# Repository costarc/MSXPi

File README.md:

# MSXPi

MSXPi is a hardware interface and software solution that lets MSX computers
control and use Raspberry Pi resources. The interface exposes I/O ports that
the MSX reads and writes, and the data appears on the Raspberry Pi side, where
a Python program (the *msxpi-server*) acts on it. Through it the MSX can reach
network drives, the internet, disk images, ROM archives, ChatGPT, an IRC
server, TCP/IP (via UNAPI) and the Raspberry Pi itself. A Raspberry Pi Zero W
or Zero 2 W is the recommended companion board.

MSXPi also exists as a virtual device for **openMSX**: the emulated MSX gets
the same commands and the same server, with no hardware at all. See
[Quick Start 2 - openMSX](#quick-start-2---openmsx-no-hardware-needed).

## 📖 The Book

The complete design and implementation of MSXPi is documented in a book:

**Anatomy of an Interface: MSXPi, a Case Study in Hardware/Software Co-Design**

It follows one real system, from the cartridge bus and the programmable logic to the
Python server on the Raspberry Pi and the applications on the MSX, and shows how each layer
was designed, built and tested. No MSX knowledge is assumed, and you do not need the board:
the whole system runs in the openMSX emulator on a PC.

The book covers:

* Design decisions and trade-offs
* Hardware architecture
* CPLD design (VHDL) and the Z80 bus interface
* Software implementation: Z80 assembly on the MSX, Python on the Raspberry Pi
* The LINK2 protocol and interface specifications
* Testing on real hardware and in openMSX
* Engineering lessons learned during development

### 👉 [Get the book on Amazon](https://link.amazon/B0eOuqOcq)

<sub>As an Amazon Associate, the author earns from qualifying purchases. Buying through this link
supports the MSXPi project at no extra cost to you.</sub>

> [!CAUTION]
> **Version 1.7.0 breaks compatibility with every earlier MSXPi ROM.**
> **Every MSXPi EEPROM must be rewritten with the 1.7.0 ROM** (`software/target/msxpi32k.rom`, written with
> `at28c256`, see [Step 2](#step-2---write-the-rom-to-the-eeprom-with-at28c256com)) before it is used with
> this release. Upgrade the whole set together: the ROM, the msxpi-server and the client commands (`.COM`
> files). Version 1.7.0 moves every transfer between the MSX and the Pi to LINK2, a new protocol with
> CRC-16 checked blocks; the new `.COM` files do not work with an older server. The CPLD firmware is
> unchanged (v1.6). To stay on an older ROM, use the server from the matching `release/vX.Y` branch.

Version 1.7.0 is the current release. What changed is in
[Release_Notes](Release_Notes); how to use everything is in the
[documents](documents) folder.

> **Notice: online gaming is in alpha testing.** The online games (PLAYNET and MCHAT game invitations,
> for example Konami's Soccer over the Internet) are experimental and **not ready for end users yet**.
> They have only been tested between emulators, expect bugs and missing pieces, and the files, commands and
> protocols may still change. Try them if you want to help test, but do not rely on them.
>
> `MCHAT` plays through the MSXPi when there is one, and over TCP/IP UNAPI (InterNestor Lite on the MSXPi's Ethernet, or a
> hardware stack such as GR8NET) when there is not. `MCHAT /T` forces TCP/IP even with an MSXPi. TCP/IP play needs a memory
> mapper (MSR or Nextor); see the users' guide section "Online games" for the requirements.

**CPLD firmware.** Version 1.7.0 uses the v1.6 CPLD firmware; a board already on
v1.6 needs no CPLD change. On older CPLD firmware the 1.7.0 ROM still works, using
the slower polled transfers.

**About the DOS.** MSXPi's own ROM contains **MSX-DOS 1 (1.03) only**. It does not
contain Nextor or MSX-DOS 2. MSXPi *coexists* with them: Nextor or MSX-DOS 2 come
from another disk interface in the same MSX (for example a MegaFlashROM SCC+ SD),
and MSXPi's commands, BASIC extension and UNAPI work alongside them. The
EEPROM holds two ROMs, picked with the bank jumper: MSX-DOS 1 (**BANK2**) or
the BIOS only - `CALL MSXPI` and the Ethernet UNAPI in ROM, no disk system
(**BANK1**) - for use next to Nextor / MSX-DOS 2. With the MSX-DOS 1 ROM the
Ethernet UNAPI driver is loaded from disk (`ETHUNAPI.COM`).

Contents

1. [How the pieces fit together](#how-the-pieces-fit-together)
2. [Quick Start 1 - Real hardware](#quick-start-1---real-hardware-msxpi-interface--raspberry-pi)
3. [Quick Start 2 - openMSX](#quick-start-2---openmsx-no-hardware-needed)
4. [Using MSXPi: the p commands](#using-msxpi-the-p-commands)
5. [Bugs and known limitations](#bugs-and-known-limitations)
6. [Repository structure](#repository-structure)

How the pieces fit together
===========================

    Real hardware:
    MSX  <-- I/O ports $56 $57 $5A -->  MSXPi interface  <-- GPIO -->  Raspberry Pi
    (p.com, pcopy, msxarch,             (CPLD + EEPROM with            (msxpi-server.py,
     BASIC CALL MSXPI, ROM BIOS)         the MSXPi ROM)                 Python 3)

    openMSX:
    MSX  <-- I/O ports $56 $57 $5A -->  MSXPiDevice      <-- TCP :5000 --> msxpi-server.py
                                        (emulated CPLD)                    (on your PC)

* **MSX side** - the ROMs in the interface's 32 KB EEPROM and the `.COM`
  programs that you copy to your MSX disk or SD card. The EEPROM image,
  `msxpi32k.rom`, holds two 16 KB ROMs:
  * `msxpibios.rom` - MSXPi BIOS, MSX-DOS 1 disk driver, `CALL MSXPI` for
    BASIC (the Ethernet UNAPI driver no longer fits here: load
    `ETHUNAPI.COM` for TCP/IP);
  * `msxpibas.rom` - the BIOS without the disk system: `CALL MSXPI` and the
    Ethernet UNAPI.
* **Interface** - a CPLD decodes ports $56/$57/$5A and shifts bytes to and
  from the Pi; since v1.6 it also holds the Z80 /WAIT line while a byte is in
  flight, so the MSX can move data with INIR/OTIR.
* **The link** - since 1.7.0 every transfer uses LINK2: framed blocks with a
  CRC-16 (CCITT-FALSE), acknowledged one by one and resent when damaged
  (`documents/LINK2-DESIGN.md`).
* **Server side** - `msxpi-server.py`, which runs on the Pi (GPIO link) or on
  your PC next to openMSX (TCP socket link). Everything it needs lives in one
  folder, the *MSXPi home directory*: `/home/pi/msxpi`.

Quick Start 1 - Real hardware (MSXPi interface + Raspberry Pi)
==============================================================

You will need:

* An MSXPi interface (built from `hardware/`; assembly notes in
  `documents/MSXPi Assembly Instructions.txt`) with an AT28C256 EEPROM.
* A Raspberry Pi Zero W / Zero 2 W (not a Pico - it cannot run Linux), with
  the 40-pin header on the side that matches your PCB, a micro SD card of 8 GB
  or more, and a PC to prepare it.
* An MSX with a disk or SD interface running MSX-DOS 1, MSX-DOS 2 or Nextor
  (MSXPi itself only has MSX-DOS 1 in its ROM; MSX-DOS 2 / Nextor must come
  from that other interface),
  and a way to copy files from your PC onto that disk. A second disk interface
  (Nextor / MSX-DOS 2) next to MSXPi is the best way to use it.
* Only if the CPLD is not programmed yet: an Altera USB-Blaster and Quartus
  13.0 SP1 on Windows.

Do the steps in order. Each ends with a check, so you know where a problem is.

### Step 1 - Program the CPLD (skip if it is already programmed)

1. Connect the USB-Blaster to the JTAG connector of the interface. The
   interface must be in the MSX slot and the MSX switched on.
2. In Quartus: Tools -> Programmer, mode JTAG, *Add File*, pick the `.pof` for
   your board, tick *Program/Configure* and *Verify*, *Start*.

   | Board | File (in `hardware/CPLD_Project`) |
   |---|---|
   | V1.3 Rev.1 (and boards built for v1.3 to v1.5) | `MSXPi_v1.6.pof` |
   | V1.1 Rev.1, V1.2.1b | `v1.1/MSXPi_v1.6_wait.pof` |
   | v0.8.2 / v1.0 (PCB v0.7 Rev.7) | `v0.8.2/MSXPi_v1.6_polled.pof` |

3. **Check:** in MSX BASIC, `PRINT INP(&H57)` must not print 254 or 255 (that
   means no CPLD answered); `p ver` shows the same build ID in readable form later. Older boards need a few extra settings - see
   `hardware/CPLD_Project/LEGACY_BOARDS.md` and `documents/Legacy Support.odt`.

### Step 2 - Write the ROM to the EEPROM with AT28C256.COM

The EEPROM (32 KB) holds `msxpi32k.rom`: two 16 KB ROMs, one per bank. It is
written from the MSX itself, so you need a working MSX with a disk drive and
the interface plugged in. The Raspberry Pi does not need to be attached yet.

| Bank jumper (as on the PCB) | EEPROM half | ROM | The MSX gets |
|---|---|---|---|
| **BANK2** (EEPROM A14 = CPU A15) | lower | `msxpibios.rom` | MSX-DOS 1 from the Pi, `CALL MSXPI` (Ethernet UNAPI from `ETHUNAPI.COM`) |
| **BANK1** (EEPROM A14 = CPU A14) | upper | `msxpibas.rom` | `CALL MSXPI` and Ethernet UNAPI, no disk system and no extra drives |

1. Copy `software/target/at28c256.com` and `software/target/msxpi32k.rom` to
   your MSX disk or SD card. (Both are also on the MSXPi boot disk.)
2. Set the bank jumper to **BANK2**. The EEPROM can only be programmed in
   that position: the chip's write-protection commands only reach the right
   addresses when its A14 follows CPU A15.
3. Boot MSX-DOS (from your disk interface) and list the ROMs the tool can see:

        at28c256 /i

   If the interface already holds a bootable ROM, remove its enable jumper
   (`SLTSL`, `CS12` on some boards) first, otherwise the MSX finds it, boots
   from it and the tool cannot write. Note the slot number of the interface.
4. Write the ROM (2 is the slot number here; use yours):

        at28c256 /s 2 msxpi32k.rom

   Always write the whole 32 KB file in one go: the tool erases the entire
   chip before writing, so writing one 16 KB ROM on its own wipes the other
   bank. The tool write-protects the EEPROM (software data protection) when
   it is done. If your chip fails to program, repeat with `/r`, which writes
   slowly.
5. Switch the MSX off and set the jumpers for how you will use it:

   * **Booting MSX-DOS 1 from a disk image on the Pi:** close `SLTSL`, bank
     jumper on **BANK2**. The Pi must finish booting first, so the first cold
     boot takes a few minutes. Press ESC during boot to go straight to BASIC.
   * **With another disk interface (recommended):** close `SLTSL`, bank
     jumper on **BANK1**, and put MSXPi in a higher slot than the disk
     interface. The MSX boots Nextor / MSX-DOS 2 from the other interface;
     MSXPi adds no drives and uses almost no memory, and `CALL MSXPI` in
     BASIC and the Ethernet UNAPI (in this ROM) are available.
   * **MSXPi ROM off:** remove `SLTSL`. MSXPi then works only through the
     `.COM` commands - no `CALL MSXPI`; for TCP/IP load `ETHUNAPI.COM`.

   The EEPROM answers in every page of its slot, so the bank that is not
   selected appears at 8000h. The two ROMs are built to tolerate each other
   there; always write them together, from the same `msxpi32k.rom`.
6. **Check:** in BASIC, `CALL MSXPIVER` prints the ROM version; with BANK1 it
   ends in "(no DOS)".

### Step 3 - Prepare the Raspberry Pi

Install a fresh Raspberry Pi OS Lite and run the MSXPi setup script. (The
old ready-made SD card image is no longer offered.)

1. Write *Raspberry Pi OS Lite (32-bit)* to the SD card with Raspberry Pi
   Imager (https://www.raspberrypi.com/software). In its settings choose user
   name `pi`, enable SSH and enter your WiFi details.
2. Boot the Pi, log in (SSH, or keyboard and HDMI) and run:

        wget https://tinyurl.com/MSXPi-Setup
        chmod 755 MSXPi-Setup
        bash ./MSXPi-Setup

   The script checks the Pi, the network and the clock, installs everything
   below, starts the server, checks that it runs, and reboots (a few minutes).
   It asks which board you have; to skip the question add `--board v1.3`,
   `--board v1.1` or `--board old` (see the table below). `--help` lists the
   other options (WiFi, `--no-reboot`, ...). It is safe to run again: it
   updates the server and repairs what is missing, and never overwrites
   `msxpi.ini`.

What the setup gives you (check it, or do it by hand):

* **Python 3** with the modules `requests`, `fs` and `RPi.GPIO`. `fs` needs
  `pkg_resources`, so a `setuptools` older than version 81 must be present
  (`python3 -m pip install fs "setuptools<81" --break-system-packages` if you do it
  by hand). The packages `unar`, `lhasa`, `unzip`, `mpv`, `alsa-utils` and
  `smbclient` are for unpacking archives, playing audio and reading network
  shares; `iptables` gives the MSX its network; `gcc` builds the native GPIO
  engine. PChess also needs the Python package `chess`
  (`requirements-pchess.txt`); the rest of the server works without it.
* **The MSXPi home directory `/home/pi/msxpi`**, owned by user `pi`. The path is
  built into the server (the environment variable `MSXPI_HOME` overrides it).
  It holds:

  | File | Purpose |
  |---|---|
  | `msxpi-server.py` and the `msxpi_*.py` modules (`msxpi_cmd_*.py`, `msxpi_transport.py`, `msxpi_settings.py`, ...), `mapper_detect.py` | the server and its modules |
  | `native/` | the native GPIO library `libmsxpi_gpio.so`, built on the Pi (without it the server falls back to slower Python GPIO and says so in its log) |
  | `msxpi.ini` | your settings, see below |
  | `disks/msxpiboot.dsk`, `disks/tools.dsk` | drives A: and B: for the MSX-DOS 1 boot mode |
  | `msxpi-monitor`, `msxpi-tcpip-setup.sh`, `update.sh` | helpers |

* **A systemd service** (`msxpi-monitor`) that starts the server at boot. To
  watch it work, run it by hand: `cd /home/pi/msxpi && python3 msxpi-server.py`.
* **msxpi.ini**, copied from the template that matches your PCB
  (`software/Server/Python/src`):

  | Board | Template |
  |---|---|
  | V1.3 (and later) | `msxpi-JumperRight.ini` |
  | V1.1 Rev.0 | `msxpi-JumperRight_PCBV1.1Rev.0.ini` |
  | Older boards | `msxpi-JumperLeft.ini` |

  A board **without** the shutdown push-button needs `var RPI_SHUTDOWN=none`.
  Optional keys: `OPENAIKEY` and `OPENAIMODEL` (ChatGPT), `RAPIDAPIKEY`,
  `FINNHUBKEY`, `TWELVEDATAKEY`, `ALPHAVANTAGEKEY` (stock quotes),
  `WIFISSID`, `WIFIPWD`, `WIFICOUNTRY`. From the MSX you can change any of
  them with `p set NAME value`.

Insert the SD card, plug the Pi into the interface **with its component side
facing you**, and switch the MSX on. The interface LED lights when the server
is running.

### Step 4 - Copy the MSX-side programs

Copy the contents of `software/target` (at least `p.com`, `pcopy.com`,
`msxarch.com`, `msxarch.ini`, `LOADROM.COM`, `ETHUNAPI.COM`, `INL.CFG` and
the `.BAS` programs) to your MSX disk or SD card. They must all come from the
same release as the ROM and the server.

**Check:** at the MSX-DOS prompt type

        p ver

It prints the board (build ID, CPLD, `/WAIT` yes or no) and the server version.
"Connection error" means the Pi is still booting (the first boot may take three
minutes), the interface is not seated, or the ROM and server versions do not
match. Press CTRL+ESC, wait five seconds, and try again. A "protocol error"
means the server is older than 1.7.0 and cannot speak LINK2: update the server.

### Step 5 - Connect to WiFi and the network

        p set WIFISSID Your Wifi Name
        p set WIFIPWD YourWifiPassword
        p wifi set
        p reboot

`p wifi` alone lists the interfaces and addresses. For TCP/IP programs (UNAPI:
InterNestor Lite, telnet, HGET) the MSX needs the MSXPi Ethernet UNAPI driver,
and the Pi builds the network behind it with `msxpi-tcpip-setup.sh` when the
server starts. If the Pi had no default route at boot, run `p netreset`. Then,
depending on how the MSX was started:

| ROM bank / DOS | Type, in this order |
|---|---|
| **BANK2**, MSX-DOS 1 booted from MSXPi | `MSR I`, `ETHUNAPI`, `INL I` |
| **BANK1**, MSX-DOS 1 from another interface | `MSR I`, `INL I` |
| **BANK1**, Nextor or MSX-DOS 2 | `RAMHELPR I`, `INL I` |

then `HOST GOOGLE.COM`. With BANK1 the driver is in the ROM and `ETHUNAPI`
refuses to load. Under MSX-DOS 1 never run `RAMHELPR`: `MSR` installs the RAM
helper itself and fails if one is already there.

`HOST` printing an address means the whole path works. `p wlanreset` resets the
Pi's WiFi. Details: `software/UNAPI/README.md`.

### Step 6 - Try it

        p dir /home/pi/msxpi
        p run uname -a
        pcopy m:p.com
        msxarch                     (browse and start ROM games from the network)
        LOADROM game.rom /N
        p chatgpt Tell me a fun fact about MSX

### Updating

* MSX disk (the `.COM` files): run `msxpiupd.bat` (network required).
* To update from another git branch (client files, ROMs and server), give its name: `msxpiupd feature/name`.
  Without a name it is master. Files that exist only in the branch are not copied.
* Server: run the setup script again, from the Pi or from the MSX:

        p run wget https://tinyurl.com/MSXPi-Setup
        p run chmod 755 MSXPi-Setup
        p run sudo ./MSXPi-Setup

* ROM: the updater downloads it but never writes it - repeat Step 2.

Update all three together: the ROM, the server and the clients (`.COM` files, including `playnet.com`, `playnet.ovl`
and `mchat.com`) come from the same build, so a server update also means flashing `msxpibios.rom` again. Run `p shut` before you switch the MSX off: the Pi is
powered by the MSX, and an SD card can be corrupted by a sudden power cut.

More detail with pictures: `documents/Quick Start.odt` and the "Hard Way" tutorial
(installing Raspberry Pi OS from scratch; Portuguese version available) in the
`documents` folder.

Quick Start 2 - openMSX (no hardware needed)
============================================

The MSXPi device for openMSX emulates the interface, including the CPLD /WAIT
flow control, and talks over a local TCP socket to the same `msxpi-server.py`
that runs on the Pi. The p commands, BASIC, msxarch, ChatGPT and UNAPI
networking all work as on real hardware, and what you write under openMSX runs
unchanged on the real interface.

### Windows: install everything in one step

1. Download
   [`msxpi-openmsx-install.bat`](https://raw.githubusercontent.com/costarc/MSXPi/master/software/Server/Setup/msxpi-openmsx-install.bat)
   (right-click the link, *Save link as*) and double-click it. It needs no
   administrator rights, and downloads everything from this repository and
   from the MSXPi build of openMSX.
2. It installs Python 3 and the packages the server uses, 7-Zip, Stockfish
   and mpv (with winget), then:
   * `C:\home\pi\msxpi` - the server, `msxpi.ini` and the `disks` folder
   * `C:\home\pi\msxpi\openMSX` - openMSX with the MSXPi device, the
     `MSXPi.xml` extension and `msxpibios.rom`
   * `C:\home\pi\msxpi\start-openmsx.bat` and an **MSXPi** desktop shortcut
3. Double-click the **MSXPi** shortcut. It starts the server in its own window,
   then openMSX as a Panasonic FS-A1WSX with the MSXPi and 4 MB RAM
   extensions. The MSX boots MSX-DOS from the MSXPi boot disk
   (`disks\msxpiboot.dsk`); no floppy image is needed.
4. Go on with [Step 4 - Try it](#step-4---try-it).

Notes:

* **Machine ROMs.** openMSX ships only the free C-BIOS ROMs. The FS-A1WSX
  needs its own system ROMs: put them in
  `%USERPROFILE%\Documents\openMSX\share\systemroms` (or in
  `C:\home\pi\msxpi\openMSX\share\systemroms`).
* **Internet on the MSX.** Run the installer with `-Network` (from a command
  prompt: `msxpi-openmsx-install.bat -Network`). It also installs the TAP
  driver, which asks for administrator rights once, and the launcher then sets
  up the MSX network when needed. See
  [Internet from the MSX in openMSX](#internet-from-the-msx-in-openmsx-windows).
* **Updating.** Run the installer again. It refreshes the server, the ROM and
  the extension, and replaces openMSX when a newer MSXPi build is required. It
  keeps `msxpi.ini` and the disk images.

Steps 1 to 3 below are the manual installation, for Linux and macOS or to set
things up by hand on Windows.

### Step 1 - Install openMSX with the MSXPi device

The official openMSX lives at https://github.com/openMSX/openMSX
(binaries and documentation at https://openmsx.org). The MSXPi device is not in
the official build yet, so download openMSX from the MSXPi fork instead:

* **https://github.com/costarc/openMSX/releases** - take the newest release for
  your operating system; the notes of each release say what it contains. Unpack
  it anywhere. It includes the MSXPi extension (`MSXPi.xml`) and the matching
  `msxpibios.rom`.
* Use the fork release, the `msxpibios.rom`, and the server from the same MSXPi
  version - the device, ROM and server share one protocol.
* If you keep your own openMSX, the two data files are also in this repository:
  `software/openMSX/share/extensions/MSXPi.xml` goes to openMSX's
  `share/extensions`, and `software/target/msxpibios.rom` goes to
  `share/systemroms` (the XML checks its sha1). The `MSXPiDevice` itself is only in
  builds of the fork.
* Two more extensions come from the same build (`software/build`, openMSX
  stage): `MSXPiBasic` - the BIOS-only ROM (`msxpibas.rom`), as on a board with
  the jumper on BANK1 - and `MSXPi32K`, the whole 32 KB EEPROM with the board's
  jumpers as openMSX settings, read at reset:
  `set msxpirom_bank BANK2|BANK1` (default BANK2) and
  `set msxpirom_sltsl ON|OFF` (default ON). `MSXPi32K` needs a fork build with
  EEPROM support in `MSXPiDevice` (branch `feature/msxpi-eeprom-jumpers`).

### Step 2 - Python and the MSXPi home directory

* **Python 3** (3.9 or newer; on Windows from python.org or the Microsoft
  Store, with *Add to PATH*).
* **Python modules:** `python -m pip install requests` is all the server needs
  to start. Some commands need more: `certifi` and `chess` for pchess, `Pillow`
  and `playwright` (then `python -m playwright install chromium`) for
  renderpage.
* **7-Zip** (`7z.exe` on the PATH) for zip, lzh, pma and 7z archives, used by
  msxarch and `pcopy /z`. On Linux/macOS install `p7zip`, `lhasa` and `unar`.
* **The MSXPi home directory.** The server has `/home/pi/msxpi` built in
  (set `MSXPI_HOME` to use another folder). On Linux and macOS create that
  folder. On Windows the path resolves on the *current drive*, so create
  `C:\home\pi\msxpi` and start the server from drive C:. Put in it:
  `msxpi-server.py`, `mapper_detect.py` and every `msxpi_*.py` module (all from
  `software/Server/Python/src`; the server imports them from its own folder), `msxpi.ini` (copy `msxpi-JumperLeft.ini`
  and rename it), and a `disks` folder with `msxpiboot.dsk` and `tools.dsk` from
  `software/target/disks`.
* Add the keys you need to `msxpi.ini` (for example `OPENAIKEY` for ChatGPT).
  Commands that only make sense on a Pi (`wifi`, `reboot`, `shut`, `play`) answer
  "Command not supported on this platform".

### Step 3 - Start the server, then openMSX

        cd C:\home\pi\msxpi           (Linux/macOS: cd /home/pi/msxpi)
        python msxpi-server.py

The server listens on TCP port **5000**. Now prepare a folder that openMSX uses
as disk A:. Call it `FloppyA`, copy `MSXDOS.SYS` and `COMMAND.COM` from
`software/target/disks` into it, and add the MSXPi commands from
`software/target`. Then start openMSX with the extension:

        openmsx -machine Panasonic_FS-A1WSX -ext MSXPi -diska FloppyA

Any MSX2 with 64 KB RAM will do, and Nextor on an SD/IDE image works too.
The fork also has an `MSXPiNoROM` extension (the ports without the ROM), for
trying `BLOAD"MSXPIEXT.BIN",R` the way an interface without an EEPROM is used.

**Optional: a different port.** The device takes the TCP port from the openMSX
setting `msxpiserver_port` (default 5000). Change it in the openMSX console
(F10) and the device reconnects at once:

        set msxpiserver_port 5001

Make the server listen on the same port with the environment variable
`MSXPI_PORT` (for example `set MSXPI_PORT=5001` on Windows before starting it). Use this when port 5000 is taken, or to run two
emulators with two servers.

### Step 4 - Try it

At the MSX-DOS prompt:

        p ver
        p dir /
        p set
        msxarch
        p chatgpt Tell me a funny fact about MSX

`p ver` reports `/WAIT: yes (burst)` when the device emulates the wait flow
control. "Connection error" means the server is not running, the ports differ,
or the ROM and server versions do not match. Read the log window of the server:
it prints every command it receives.

### Internet from the MSX in openMSX (Windows)

The MSXPi extension carries real network traffic, so InterNestor Lite, telnet,
HGET and the other UNAPI clients work in the emulator exactly as they do on
hardware. The emulated MSX gets its own subnet (192.168.99.0/24) and Windows
NATs it out through whichever interface carries your default route - the same
arrangement the Raspberry Pi uses, and for the same reason: bridging cannot
work over WiFi, because an access point will not forward frames whose source
MAC is not the associated station's.

This works best with an openMSX whose MSXPi device implements the v1.6
hardware /WAIT flow control (openMSX/openMSX#2194). An older build still
works: the ROM probes for wait mode, does not find it, and falls back to the
polled transport - the same path MSXPi has always used under emulation. What
you lose is the v1.6 speedup, not the connection.

**With the Windows installer**, run it with `-Network` instead of steps 1 and
2: it installs the TAP driver, and the MSXPi desktop shortcut sets up the
network (asking for administrator rights) whenever it is missing, including
after a reboot. Then go on with step 3.

#### Step 1: Install the OpenVPN TAP driver

Install OpenVPN (https://openvpn.net/community-downloads/) and keep the "TAP
Virtual Ethernet Adapter" component, or install the standalone tap-windows6
driver on its own. Afterwards an adapter named "OpenVPN TAP-Windows6" appears
in Network Connections - nothing else about OpenVPN is used or needs
configuring.

#### Step 2: Run the setup once, as Administrator

From an elevated PowerShell:

          powershell -ExecutionPolicy Bypass -File software/Server/Setup/msxpi-tcpip-setup.ps1

It reports what it did:

          adapter: OpenVPN TAP-Windows6  [TAP-Windows Adapter V9]
          uplink: Wi-Fi
          OpenVPN TAP-Windows6 up: 192.168.99.1/24 mtu 576
          NAT: 192.168.99.0/24 -> Wi-Fi
          dns: 192.168.1.254

and prints the InterNestor Lite settings to match. Note the "dns:" line - that
is the resolver the MSX should use.

This is NOT persistent across reboots; re-run it after a restart. To undo it
and give the adapter back to OpenVPN, add "-Down".

Windows generally allows only one NAT instance, and Docker Desktop, Hyper-V and
WSL each take one. If something already holds it the script names it and stops
rather than half-configuring.

#### Step 3: Start the server

          python msxpi-server.py

No administrator rights are needed for this part. It should print:

          eth: TAP device OpenVPN TAP-Windows6 up

If it says "TAP unavailable ... falling back to MockLink", something else has
the adapter open - a running OpenVPN session will do that. MockLink answers
every UNAPI call correctly and carries no traffic at all, so the MSX will look
configured and reach nothing.

#### Step 4: On the MSX

Start openMSX with the MSXPi extension, then:

          MSR I              (MSX-DOS 1 only - see below)
          ETHUNAPI
          INL I
          HOST GOOGLE.COM

`HOST` printing an address means the whole path works. The extension maps the
EEPROM the way the board shows it with the BANK2 jumper, so the MSX boots the
MSX-DOS 1 ROM, which has no Ethernet driver since 1.7.0: `ETHUNAPI.COM` loads
it into a mapped RAM segment. (With the BIOS-only ROM the driver is in the ROM
and ETHUNAPI refuses to load.)

**Under MSX-DOS 1, do not run RAMHELPR I.** It installs the UNAPI RAM helper on
its own, and MSR.COM installs the mapper support routines AND a helper - so MSR
then finds a helper already present and aborts, leaving INL to fail with "No
mapper support routines found". A cold boot clears it. Under Nextor or MSX-DOS 2,
skip MSR and run `RAMHELPR I` instead: the mapper routines are already there.

If `HOST` answers "8: DNS not found" but the link is otherwise up, the resolver
is the problem rather than the network - INL.CFG ships with 1.1.1.1, and some
networks block public resolvers. Use the address the setup script printed:

          INL IP P 192.168.1.254

Using MSXPi: the p commands
===========================

Type `p` with no arguments (or `p /help`) to list them. All work under MSX-DOS 1,
MSX-DOS 2 and Nextor. Paths can be on the Pi, on the network (http, https, ftp,
smb) or on one of the virtual drives set with `p set`: `m:` (your local
server), `r1:` and `r2:` (MSX1 and MSX2 ROMs on msxarchive.nl).

| Command | What it does |
|---|---|
| `p ver` | board, CPLD build and /WAIT support, then the server version |
| `p cd`, `p dir` | change and list the current path |
| `p run <cmd>` | run a command on the Pi; use `::` for a pipe |
| `p date` | set the MSX date and time from the Pi |
| `p set [NAME value]` | show or change MSXPi variables (saved in `msxpi.ini`) |
| `p wifi`, `p wifi set` | list interfaces / apply WIFISSID and WIFIPWD |
| `p wlanreset [secs]`, `p netreset [secs]` | reset the Pi's WiFi / rebuild its TCP/IP setup for UNAPI |
| `p music`, `p play`, `p vol` | audio playback and volume on the Pi |
| `p reload A:` (or `B:`) | reload a drive's disk image |
| `p reboot`, `p shut`, `p restart` | reboot / shut down the Pi, restart the server |
| `p chatgpt <question>` | ask ChatGPT (needs OPENAIKEY) |
| `p showpage [/4\|/6\|/8] <url>` | render a web page on the MSX screen |
| `pchess` | chess on an MSX2 (128 KB VRAM), local or over IRC (see `software/Client/src/PCHESS.md`) |
| `nitros` | on-demand NitrOS-9 console on the Pi with the MSXPi interface, or in openMSX on Windows/Linux, with file exchange; see [setup](documents/NITROS-Users-Guide.md) |
| `ssh user@host [port]` | interactive SSH terminal through the MSXPi Raspberry Pi; prompts and passwords appear on the MSX |
| `pcopy` | copy Pi/network file to the MSX drive (`/z` unpacks archives) or an MSX file to the Pi |
| `msxarch` | browse ROM repositories (listed in `MSXARCH.INI`) and start a game |
| `LOADROM name /N` | load a plain ROM or MegaROM from the network |
| `at28c256` | write the interface EEPROM |
| `msxpiupd.bat [branch]` | update the MSX-side files (and the server) from master or a git branch |

From BASIC use `CALL MSXPI("1,C000,dir /home/pi/msxpi")` (see `target/API.BAS`).
The full reference, with examples, is in `documents/MSXPi Users and Developers Guide.odt`.

Bugs and known limitations
==========================

* **Upgrade as a set.** The 1.7.0 ROM, server and `.COM` files are meant to be
  used together; every EEPROM must be rewritten with the 1.7.0 ROM. A 1.7.0
  `.COM` file against an older server stops with a protocol error
  (RC_PROTOERR, "server does not speak LINK2"); other mixes usually show up as
  "Connection error".
* **/WAIT bursts need a v1.6 CPLD image and a board that wires /WAIT.** Boards
  built for v0.8.2 and v1.0 (PCB v0.7 Rev.7) have no /WAIT connection and run
  the polled transfers only. Disk reads and writes both burst where /WAIT is
  available.
* **LINK2 on real hardware.** The BIOS half was soak-tested on hardware; the
  MSX-DOS 1 driver and the `.COM` tools on LINK2 were tested in openMSX, and
  their hardware checklist (`documents/LINK2-TEST-PLAN.md`, T6.7) is still open.
* **Older boards need settings**: `RPI_SHUTDOWN=none` without the push-button,
  and `GPIO_CS_SETUP_NS=1000` on the v0.8.2 board. On that board the EPROM
  /OE jumper must be on CS1, never CS12, or programs that call EXTBIO (`p`,
  `pcopy`) hang the MSX. See `hardware/CPLD_Project/LEGACY_BOARDS.md`.
* **MSXPi only carries MSX-DOS 1.** Nextor and MSX-DOS 2 are not in the MSXPi
  ROM; they run from another disk interface that MSXPi coexists with.
* **Booting MSX-DOS 1 from the Pi is slow and fragile.** It needs the Pi to
  finish booting first and depends on the disk images; use another interface
  with Nextor or MSX-DOS 2 for daily work. Do not delete files on drive A: in
  that mode.
* **A stuck transfer needs CTRL+ESC.** Hold CTRL and press ESC to abort, wait
  about five seconds while the server resynchronises, and retry. ESC alone is
  an ordinary key and never aborts a transfer. If commands keep failing, restart
  the server (`p restart`) or reboot the Pi.
* **msxarch and MegaROMs.** Mappers detected: plain, Konami, Konami SCC, ASCII8
  and ASCII16. Other mappers, ROMs that need more RAM than the MSX has, and some
  titles that rewrite their own bank switching are rejected with a reason or may
  not run. Bank-switch writes are patched by the server, so what runs is not byte-for-byte the original ROM.
* **UNAPI/TCP/IP.** With the MSX-DOS 1 ROM (BANK2) load `ETHUNAPI` after `MSR I`
  and before `INL I`; the driver is no longer in that ROM. Do not run `RAMHELPR`
  before `MSR` under MSX-DOS 1 (INL then fails with "No mapper support routines
  found"; a cold boot clears it). Run only one Ethernet driver: `ETHUNAPI` next
  to the BIOS-only ROM's driver is refused, and if it were forced the two would
  switch the server's Ethernet protocol back and forth. If
  `HOST` answers "8: DNS not found" the resolver, not the link, is the problem:
  use `INL IP P <address>`. Under openMSX on Windows the TAP setup script must be
  run again after every reboot, only one Windows NAT instance can exist (Docker
  Desktop, Hyper-V and WSL each take one), and if the server prints "falling back
  to MockLink" the MSX looks configured but reaches nothing.
* **The server on Windows and macOS** runs the commands that make sense there;
  `wifi`, `reboot`, `shut`, `play`/`music` and `vol` are Raspberry Pi only.
* **Hardware compatibility.** Some MSX models have unusual slot or bus
  implementations and may not work; MSX-DOS needs 64 KB RAM. The Pi header must
  face the correct way for your PCB (a Zero WH has its header on the wrong side
  for the standard PCB).
* **ChatGPT and stock commands** need your own API keys in `msxpi.ini`; no key
  ships with MSXPi.
* **Tests.** Server unit tests are in `software/Server/Python/tests`; the
  UNAPI harness is in `software/UNAPI/harness`.
* The PDF copies of the documents in `documents` may be older than the `.odt`
  files.

Report problems at https://github.com/costarc/MSXPi/issues.

Repository structure
====================

Branches:

    master          the most recent code; may change within minutes - expect bugs,
                    and fixes just as fast
    release/vX.Y    one branch per release (v0.8.2, v1.0, v1.1, v1.2.1b, v1.3,
                    v1.5); use these for a known-good state
    feature/*, fix/*, docs_*
                    short-lived working branches; they appear and disappear, and
                    I recommend you do not use them

Directories:

    MSXPi
    |-- software
    |   |-- asm-common
    |   |   |-- include          BIOS routines for assembly (msxpi_bios.asm, include.asm, ...)
    |   |   `-- transport        generators: the LINK2 code for C, the /WAIT burst code
    |   |-- C-common
    |   |   |-- header           msxpi.h - the C BIOS API
    |   |   `-- lib              msxpi-bios.c
    |   |-- ROM/src
    |   |   |-- BIOS             BIOS-only ROM bank (msxpibios.asm); BASIC extension (msxpiext.asm)
    |   |   `-- MSX-DOS          disk driver and MSX-DOS 1 kernel sources
    |   |-- Client/src           p, pcopy, msxarch, pchess, showpage, templates, at28c256
    |   |   `-- loadrom          the LOADROM.COM network patch
    |   |-- ROM-Patcher          ROM patch profiles used by msxarch
    |   |-- Server
    |   |   |-- Python/src       msxpi-server.py and its msxpi_*.py modules, mapper_detect.py,
    |   |   |                    ini templates, native GPIO engine (native/)
    |   |   |-- Python/tests     server unit tests
    |   |   `-- Setup            setup scripts (Pi and Windows), update.sh, msxpi-monitor
    |   |                        and its systemd unit
    |   |-- UNAPI                Ethernet UNAPI: sources, tools, INL, test harness, documentation
    |   |-- openMSX              MSXPiDevice source, extension XML, build files
    |   |-- target               everything you copy to the MSX (.COM, .BAS, ROM, disks)
    |   |-- docs                 mapper, ROM and PChess IRC design notes
    |   `-- make.bat, make.sh    build scripts for the MSX-side programs
    |-- hardware
    |   |-- CPLD_Project         VHDL, Quartus project, .pof images for every board
    |   `-- Schematic            KiCad schematic and PCB, Fabrication, BOM
    `-- documents                Users and Developers Guide, C BIOS Developers Guide,
                                 Quick Start, Legacy Support, tutorials

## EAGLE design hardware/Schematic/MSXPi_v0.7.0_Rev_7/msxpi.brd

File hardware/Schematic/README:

1.1.Rev.1 - Added jumpers to switch also SPI-RDY signal
            Added line for Reset signal - may not be safe for all MSX models
1.1.Rev.0 - Replaced Raspberry Pi mounting holes by 40 Pin Socket
      - Added jumpers to select between bit-bang GPIO and hardware GPIO pins (future use)
1.0.3 - Shifted PCB holes to better fit in Patola (Brazilian) case & added 3rd mounting hole
1.0.2 - Changed footprint to smaller size to help reducing manufacturing costs
1.0.1 - Changed ROM from 27C256 to AT28C256 with hability to be programmed from MSX-DOS
1.0 - PCB Changes from Rev.7

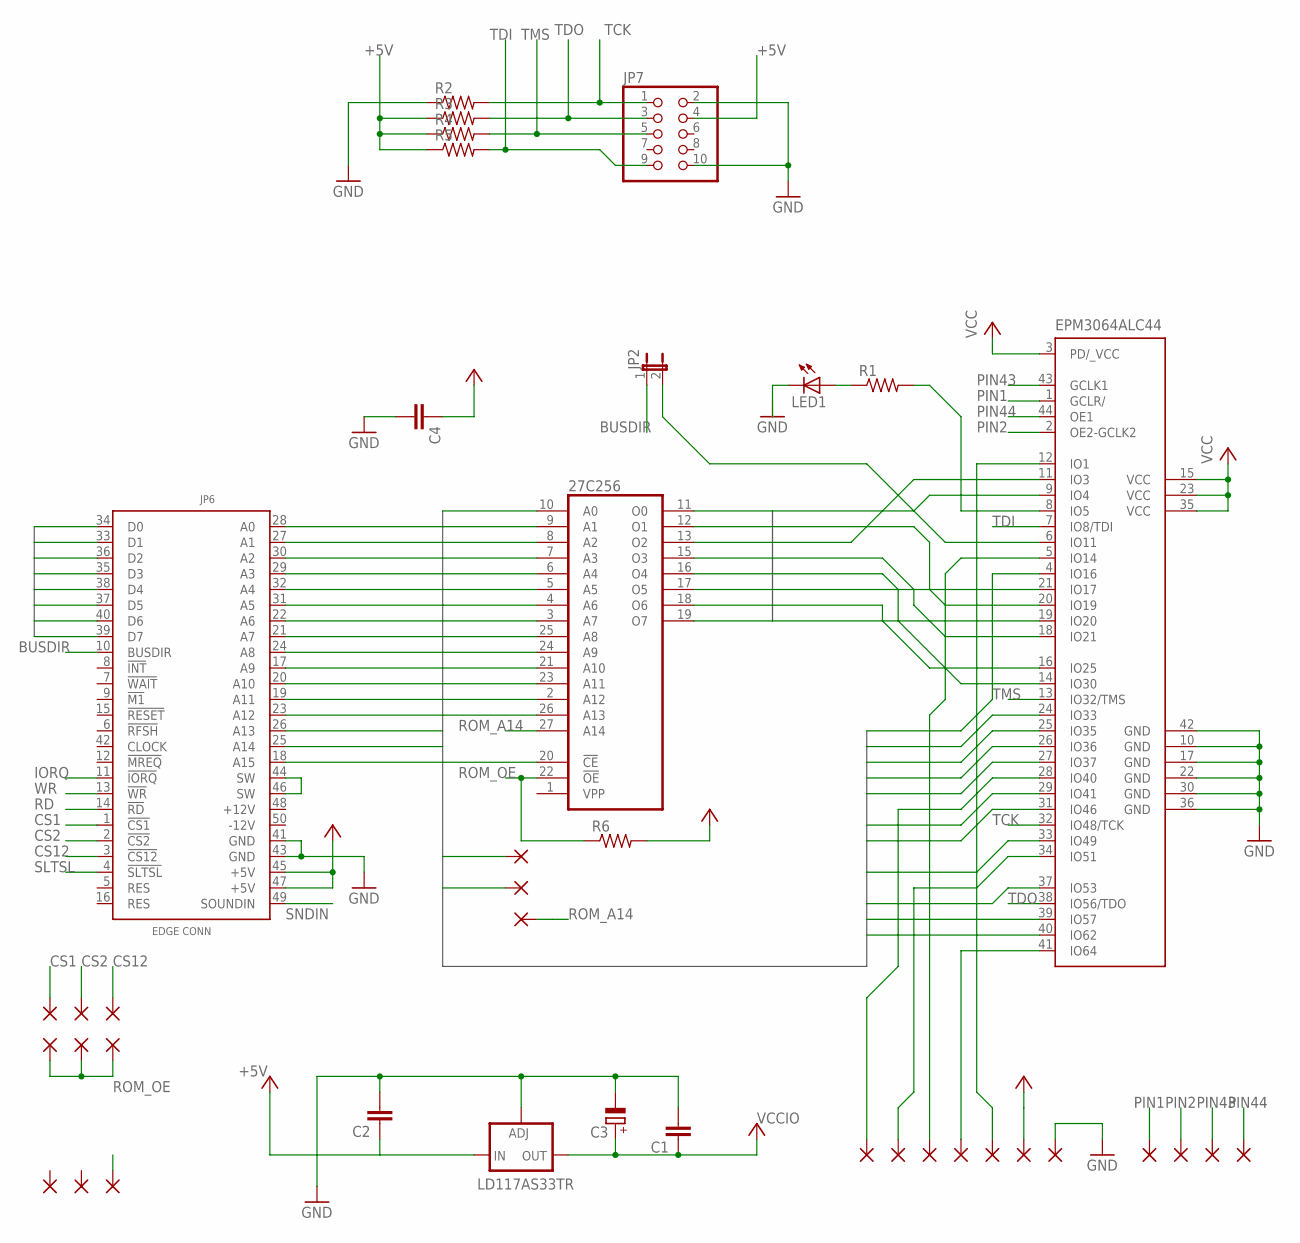
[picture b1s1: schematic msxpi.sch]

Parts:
27C256: 27256; DIL28
+5V: 2,15/1,0
A14, A15: 2,15/1,0
BUF1, BUF2: 2,15/1,0
C1, C2, C4: C2,5-3; C2.5-3
C3: CPOL-EUE2.5-5; E2,5-5
CS1, CS2, CS12: 2,15/1,0
EPM3064ALC44: EPM3064S44; PLCC-S44
GND, GND4, GND9, GND10, GND11: 2,15/1,0
IC1: LD117AS33TR; SOT223
JP2: JP1E; JP1
JP6: MSXCART1; MSXCART
JP7: PINHD-2X5/90; 2X05/90
LED1: LED3MM
PAD1, PAD2, PAD8, PAD9: 2,15/1,0
R1, R2, R3, R4, R5, R6: R-US_0207/7; 0207/7
ROMOE1, ROMOE2, ROMOE3: 2,15/1,0
ROM_OE: 2,15/1,0
SNDIN: 2,15/1,0
SPI_CS_GPIO21: 2,15/1,0

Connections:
+5V: 27C256.28 (VCC), +5V.1, C2.1, C4.1, IC1.3 (IN), JP6.45 (+5V), JP6.47 (+5V), JP7.4, R3.1, R4.1, R5.1, R6.2
A0: 27C256.10 (A0), EPM3064ALC44.31 (IO46), JP6.28 (A0)
A1: 27C256.9 (A1), EPM3064ALC44.29 (IO41), JP6.27 (A1)
A2: 27C256.8 (A2), EPM3064ALC44.24 (IO33), JP6.30 (A2)
A3: 27C256.7 (A3), EPM3064ALC44.26 (IO36), JP6.29 (A3)
A4: 27C256.6 (A4), EPM3064ALC44.25 (IO35), JP6.32 (A4)
A5: 27C256.5 (A5), EPM3064ALC44.27 (IO37), JP6.31 (A5)
A6: 27C256.4 (A6), EPM3064ALC44.33 (IO49), JP6.22 (A6)
A7: 27C256.3 (A7), EPM3064ALC44.4 (IO16), JP6.21 (A7)
A8: 27C256.25 (A8), JP6.24 (A8)
A9: 27C256.24 (A9), JP6.17 (A9)
A10: 27C256.21 (A10), JP6.20 (A10)
A11: 27C256.23 (A11), JP6.19 (A11)
A12: 27C256.2 (A12), JP6.23 (A12)
A13: 27C256.26 (A13), JP6.26 (A13)
A14: A14.1, JP6.25 (A14)
A15: A15.1, JP6.18 (A15)
BUSDIR: JP2.1, JP6.10 (BUSDIR)
CS1: CS1.1, JP6.1 (!CS1)
CS2: CS2.1, JP6.2 (!CS2)
CS12: CS12.1, JP6.3 (!CS12)
D0: 27C256.11 (O0), EPM3064ALC44.9 (IO4), JP6.34 (D0)
D1: 27C256.12 (O1), EPM3064ALC44.20 (IO19), JP6.33 (D1)
D2: 27C256.13 (O2), EPM3064ALC44.11 (IO3), JP6.36 (D2)
D3: 27C256.15 (O3), EPM3064ALC44.18 (IO21), JP6.35 (D3)
D4: 27C256.16 (O4), EPM3064ALC44.14 (IO30), JP6.38 (D4)
D5: 27C256.17 (O5), EPM3064ALC44.21 (IO17), JP6.37 (D5)
D6: 27C256.18 (O6), EPM3064ALC44.16 (IO25), JP6.40 (D6)
D7: 27C256.19 (O7), EPM3064ALC44.19 (IO20), JP6.39 (D7)
GND: 27C256.14 (GND), C1.2, C2.2, C3.-, C4.2, EPM3064ALC44.10 (GND), EPM3064ALC44.17 (GND), EPM3064ALC44.22 (GND), EPM3064ALC44.30 (GND), EPM3064ALC44.36 (GND), EPM3064ALC44.42 (GND), GND.1, IC1.1 (ADJ), JP6.41 (GND), JP6.43 (GND), JP7.2, JP7.10, LED1.K (C), R2.1
IORQ: EPM3064ALC44.40 (IO62), JP6.11 (!IORQ)
MSXR1: EPM3064ALC44.6 (IO11), JP2.2
unnamed: JP6.44 (SW), JP6.46 (SW)
unnamed: LED1.A, R1.1
unnamed: EPM3064ALC44.8 (IO5), R1.2
PIN1: EPM3064ALC44.1 (GCLR/), GND4.1
PIN2: EPM3064ALC44.2 (OE2-GCLK2), GND9.1
PIN43: EPM3064ALC44.43 (GCLK1), GND10.1
PIN44: EPM3064ALC44.44 (OE1), GND11.1
PI_RDY_GPIO25: EPM3064ALC44.12 (IO1), PAD2.1
RD: EPM3064ALC44.37 (IO53), JP6.14 (!RD)
ROM_A14: 27C256.27 (A14), ROM_OE.1
ROM_OE: 27C256.22 (!OE), R6.1, ROMOE1.1, ROMOE2.1, ROMOE3.1
SLTSL: 27C256.20 (!CE), JP6.4 (!SLTSL)
SNDIN: JP6.49 (SOUNDIN), SNDIN.1
SPI_CS_GPIO21: EPM3064ALC44.28 (IO40), SPI_CS_GPIO21.1
SPI_MISO_GPIO12: EPM3064ALC44.41 (IO64), PAD1.1
SPI_MOSI_GPIO16: EPM3064ALC44.5 (IO14), PAD9.1
SPI_SCLK_GPIO20: EPM3064ALC44.34 (IO51), PAD8.1
TCK: EPM3064ALC44.32 (IO48/TCK), JP7.1, R2.2
TDI: EPM3064ALC44.7 (IO8/TDI), JP7.9, R5.2
TDO: EPM3064ALC44.38 (IO56/TDO), JP7.3, R3.2
TMS: EPM3064ALC44.13 (IO32/TMS), JP7.5, R4.2
VCCIO: C1.1, C3.+, EPM3064ALC44.3 (PD/_VCC), EPM3064ALC44.15 (VCC), EPM3064ALC44.23 (VCC), EPM3064ALC44.35 (VCC), IC1.4 (OUT)
WR: EPM3064ALC44.39 (IO57), JP6.13 (!WR)

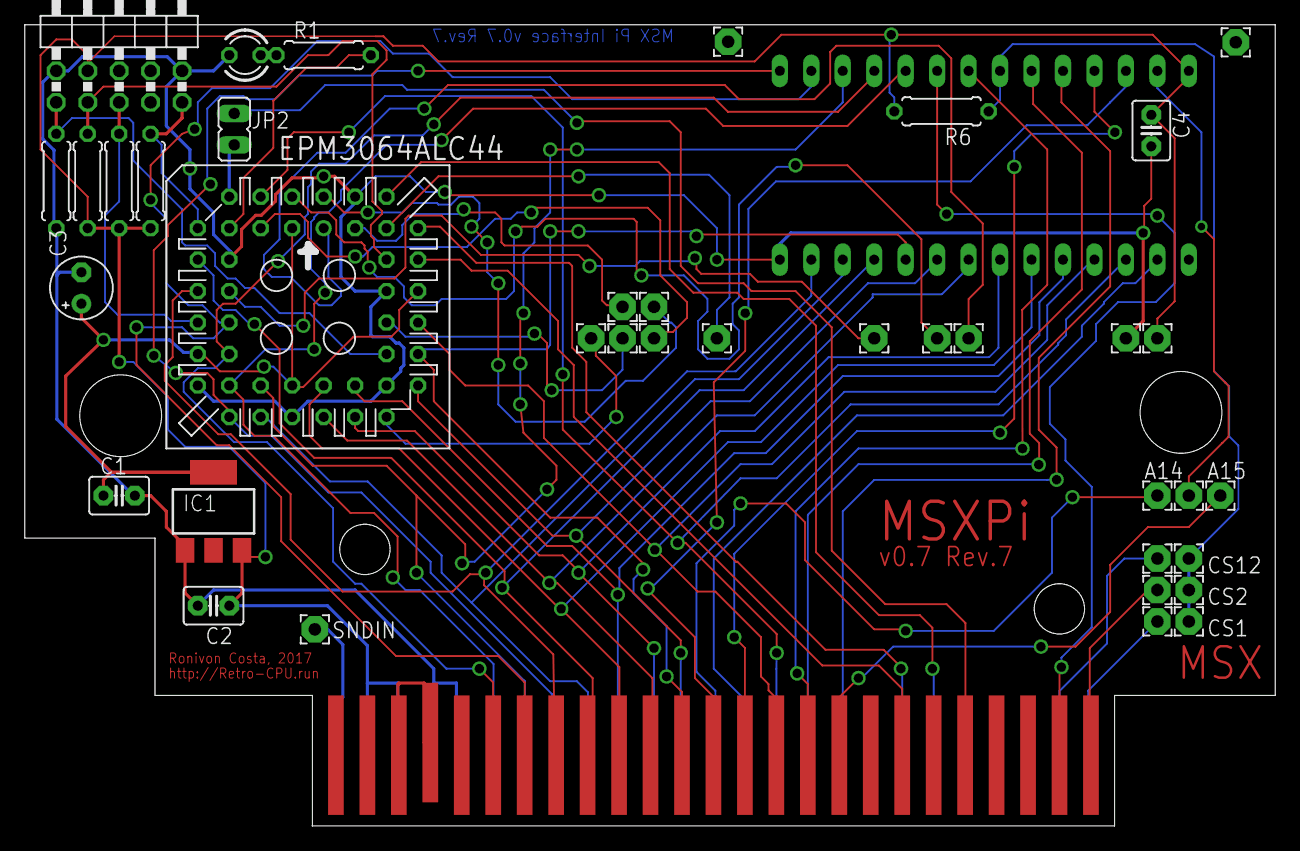
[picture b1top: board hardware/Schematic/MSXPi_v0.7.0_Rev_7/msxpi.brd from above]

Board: 2 copper layers, 101.0 x 64.7 mm, 40 parts (1 on the bottom side), 55 nets.

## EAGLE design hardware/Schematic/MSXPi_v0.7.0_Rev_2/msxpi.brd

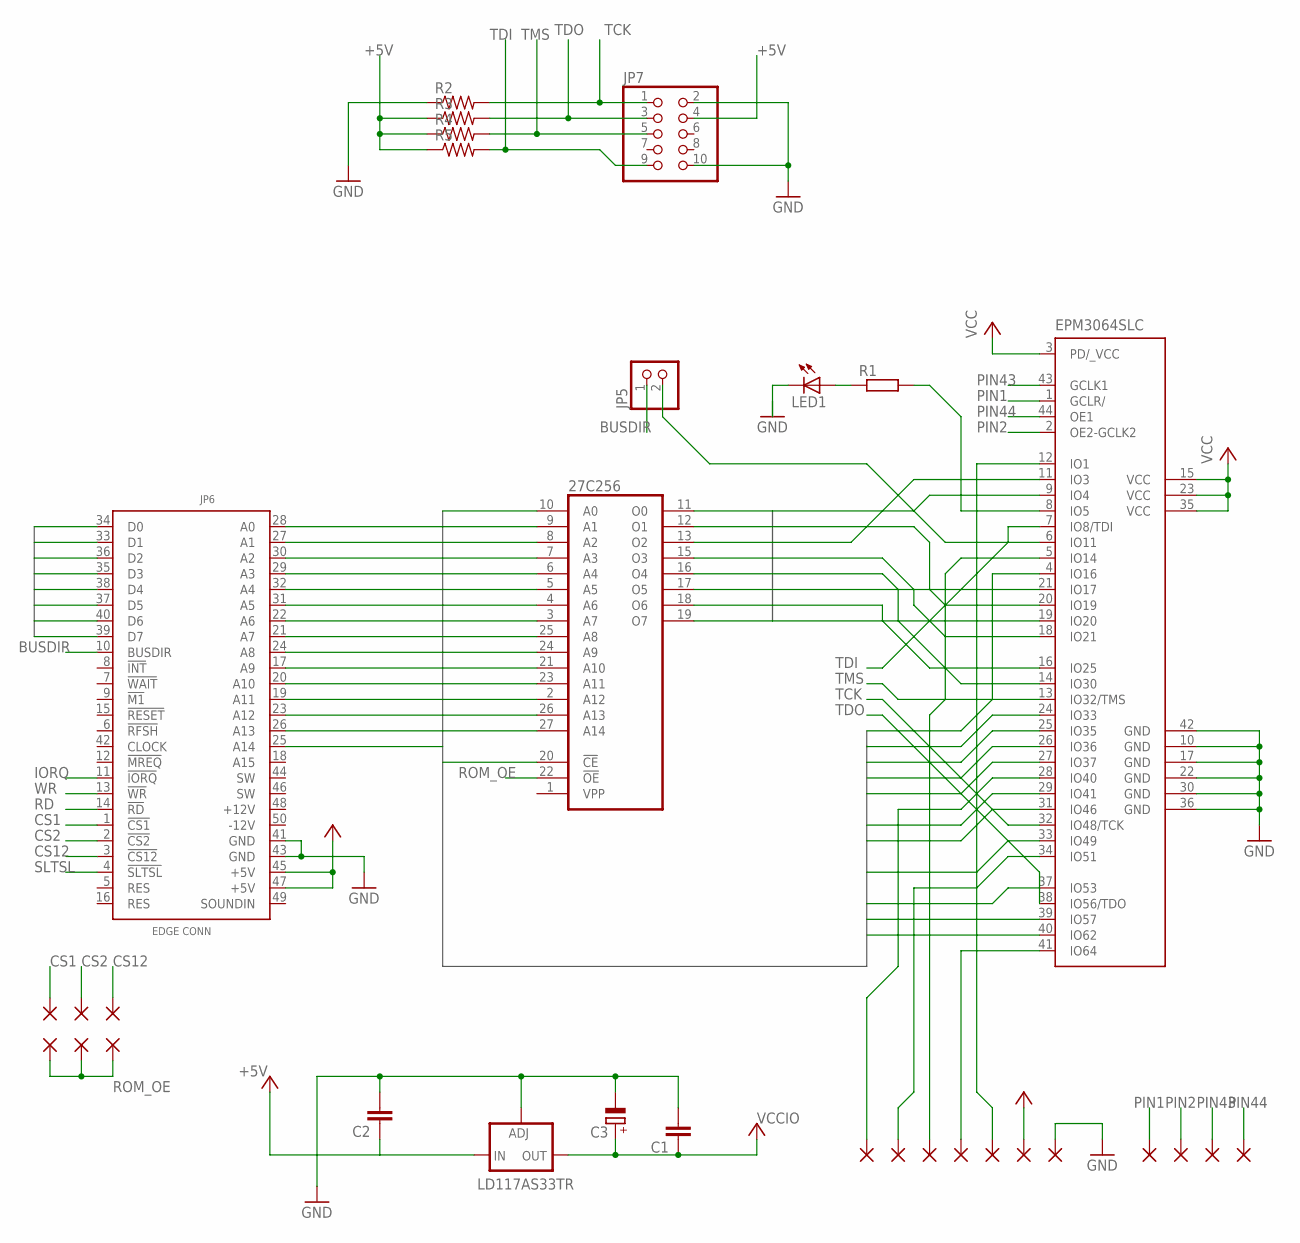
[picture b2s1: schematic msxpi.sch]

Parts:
27C256: 27256; DIL28
+5V: 2,15/1,0
C1, C2: C2,5-3; C2.5-3
C3: CPOL-EUE2.5-5; E2,5-5
CS1, CS2, CS12: 2,15/1,0
EPM3064SLC: EPM3064S44; PLCC-S44
GND, GND4, GND9, GND10, GND11: 2,15/1,0
IC1: LD117AS33TR; SOT223
JP5: PINHD-1X2; 1X02
JP6: MSXCART1; MSXCART
JP7: PINHD-2X5/90; 2X05/90
LED1: LED3MM
PAD1, PAD2, PAD8, PAD9: 2,15/1,0
R1: R-EU_0207/7; 0207/7
R2, R3, R4, R5: R-US_0207/7; 0207/7
ROMOE1, ROMOE2, ROMOE3: 2,15/1,0
SPI_CS_GPIO21: 2,15/1,0

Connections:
+5V: 27C256.28 (VCC), +5V.1, C2.1, IC1.3 (IN), JP6.45 (+5V), JP6.47 (+5V), JP7.4, R3.1, R4.1, R5.1
A0: 27C256.10 (A0), EPM3064SLC.31 (IO46), JP6.28 (A0)
A1: 27C256.9 (A1), EPM3064SLC.29 (IO41), JP6.27 (A1)
A2: 27C256.8 (A2), EPM3064SLC.24 (IO33), JP6.30 (A2)
A3: 27C256.7 (A3), EPM3064SLC.26 (IO36), JP6.29 (A3)
A4: 27C256.6 (A4), EPM3064SLC.25 (IO35), JP6.32 (A4)
A5: 27C256.5 (A5), EPM3064SLC.27 (IO37), JP6.31 (A5)
A6: 27C256.4 (A6), EPM3064SLC.33 (IO49), JP6.22 (A6)
A7: 27C256.3 (A7), EPM3064SLC.4 (IO16), JP6.21 (A7)
A8: 27C256.25 (A8), JP6.24 (A8)
A9: 27C256.24 (A9), JP6.17 (A9)
A10: 27C256.21 (A10), JP6.20 (A10)
A11: 27C256.23 (A11), JP6.19 (A11)
A12: 27C256.2 (A12), JP6.23 (A12)
A13: 27C256.26 (A13), JP6.26 (A13)
A14: 27C256.27 (A14), JP6.25 (A14)
BUSDIR: JP5.1, JP6.10 (BUSDIR)
CS1: CS1.1, JP6.1 (!CS1)
CS2: CS2.1, JP6.2 (!CS2)
CS12: CS12.1, JP6.3 (!CS12)
D0: 27C256.11 (O0), EPM3064SLC.9 (IO4), JP6.34 (D0)
D1: 27C256.12 (O1), EPM3064SLC.20 (IO19), JP6.33 (D1)
D2: 27C256.13 (O2), EPM3064SLC.11 (IO3), JP6.36 (D2)
D3: 27C256.15 (O3), EPM3064SLC.18 (IO21), JP6.35 (D3)
D4: 27C256.16 (O4), EPM3064SLC.14 (IO30), JP6.38 (D4)
D5: 27C256.17 (O5), EPM3064SLC.21 (IO17), JP6.37 (D5)
D6: 27C256.18 (O6), EPM3064SLC.16 (IO25), JP6.40 (D6)
D7: 27C256.19 (O7), EPM3064SLC.19 (IO20), JP6.39 (D7)
GND: 27C256.14 (GND), C1.2, C2.2, C3.-, EPM3064SLC.10 (GND), EPM3064SLC.17 (GND), EPM3064SLC.22 (GND), EPM3064SLC.30 (GND), EPM3064SLC.36 (GND), EPM3064SLC.42 (GND), GND.1, IC1.1 (ADJ), JP6.41 (GND), JP6.43 (GND), JP7.2, JP7.10, LED1.K (C), R2.1
IORQ: EPM3064SLC.40 (IO62), JP6.11 (!IORQ)
MSXR1: EPM3064SLC.6 (IO11), JP5.2
unnamed: LED1.A, R1.1
unnamed: EPM3064SLC.8 (IO5), R1.2
PIN1: EPM3064SLC.1 (GCLR/), GND4.1
PIN2: EPM3064SLC.2 (OE2-GCLK2), GND9.1
PIN43: EPM3064SLC.43 (GCLK1), GND10.1
PIN44: EPM3064SLC.44 (OE1), GND11.1
PI_RDY_GPIO25: EPM3064SLC.12 (IO1), PAD2.1
RD: EPM3064SLC.37 (IO53), JP6.14 (!RD)
ROM_OE: 27C256.22 (!OE), ROMOE1.1, ROMOE2.1, ROMOE3.1
SLTSL: 27C256.20 (!CE), JP6.4 (!SLTSL)
SPI_CS_GPIO21: EPM3064SLC.28 (IO40), SPI_CS_GPIO21.1
SPI_MISO_GPIO12: EPM3064SLC.41 (IO64), PAD1.1
SPI_MOSI_GPIO16: EPM3064SLC.5 (IO14), PAD9.1
SPI_SCLK_GPIO20: EPM3064SLC.34 (IO51), PAD8.1
TCK: EPM3064SLC.32 (IO48/TCK), JP7.1, R2.2
TDI: EPM3064SLC.7 (IO8/TDI), JP7.9, R5.2
TDO: EPM3064SLC.38 (IO56/TDO), JP7.3, R3.2
TMS: EPM3064SLC.13 (IO32/TMS), JP7.5, R4.2
VCCIO: C1.1, C3.+, EPM3064SLC.3 (PD/_VCC), EPM3064SLC.15 (VCC), EPM3064SLC.23 (VCC), EPM3064SLC.35 (VCC), IC1.4 (OUT)
WR: EPM3064SLC.39 (IO57), JP6.13 (!WR)

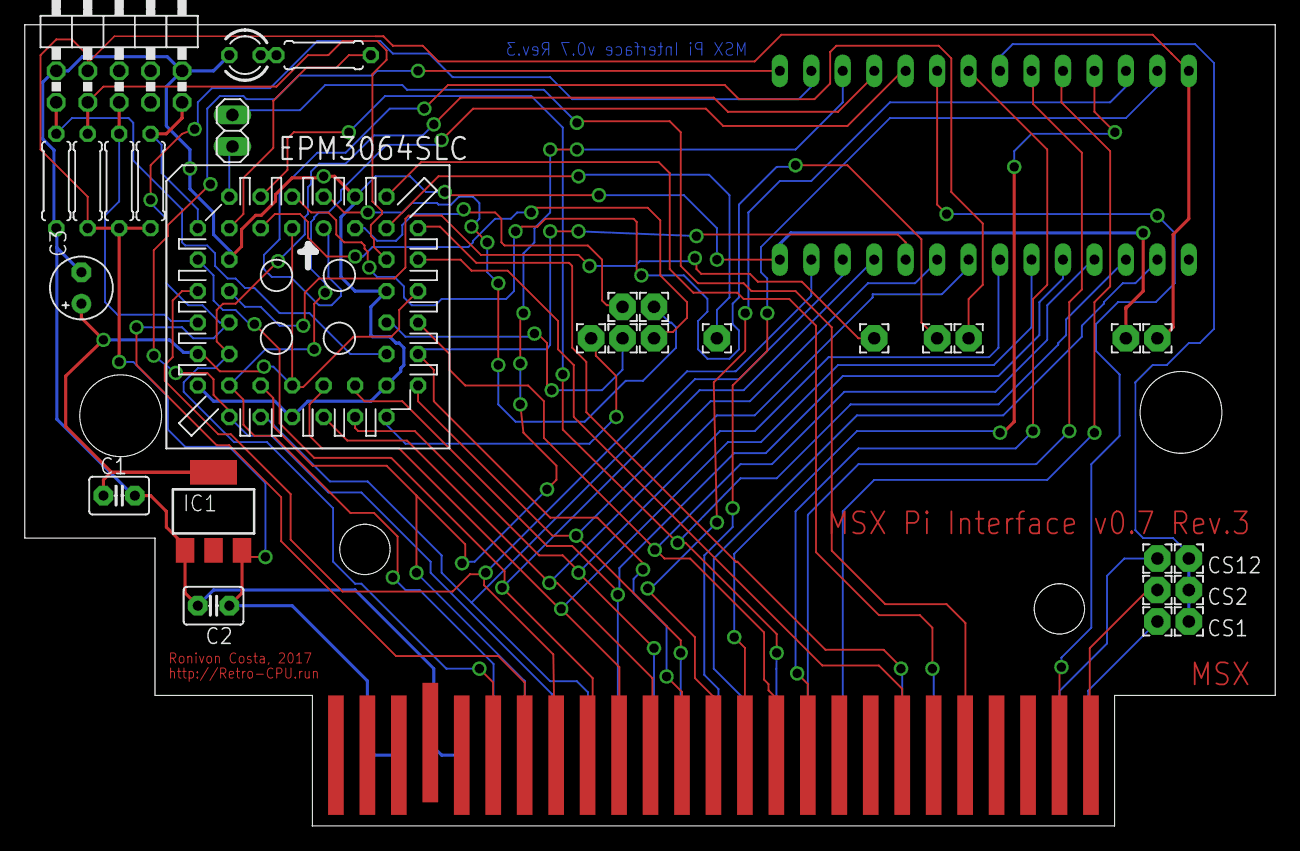
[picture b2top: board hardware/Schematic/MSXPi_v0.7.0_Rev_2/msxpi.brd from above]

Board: 2 copper layers, 101.0 x 64.7 mm, 32 parts (1 on the bottom side), 51 nets.
